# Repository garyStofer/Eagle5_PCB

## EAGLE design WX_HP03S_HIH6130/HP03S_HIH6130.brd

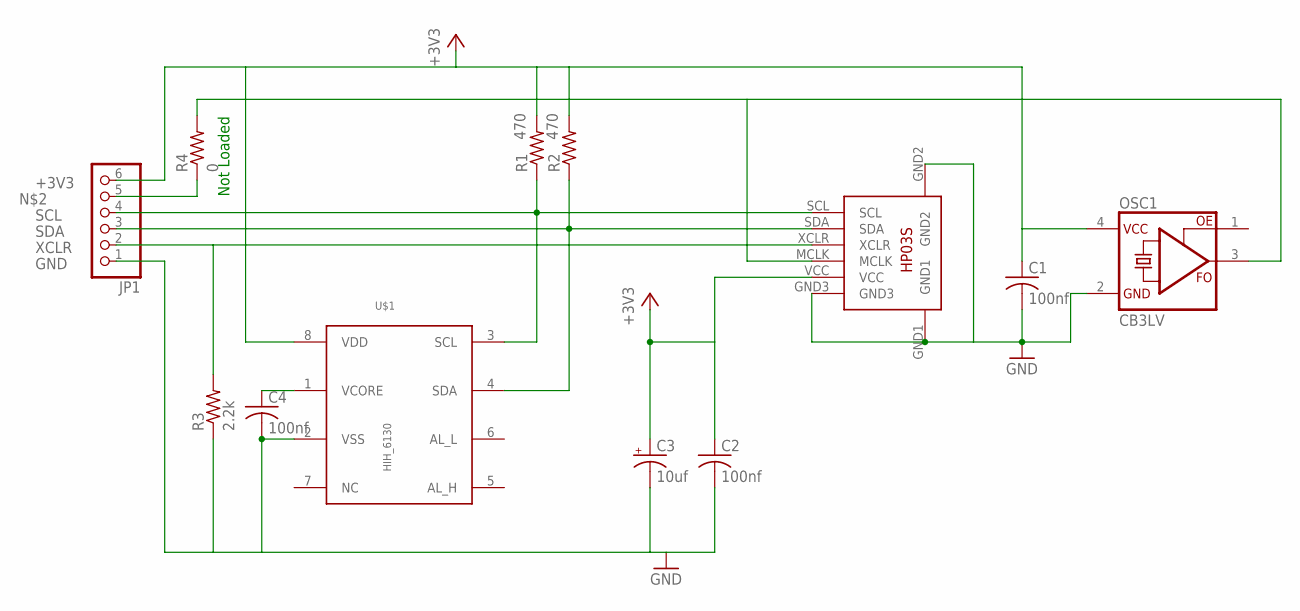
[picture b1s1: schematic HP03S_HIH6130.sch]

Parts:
C1: 100nf; C0805
C2, C4: 100nf; C0805K
C3: 10uf; SMC_P
JP1: PINHD-1X6; 1X06
OSC1: CB3LV; SMD7.5X5MM
R1, R2: 470; R0603
R3: 2.2k; R0603
R4: 0; R0603
U$1: HIH_6130; SOIC8
U$2: HP03S

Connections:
+3V3: C1.1, C2.1, C3.+, JP1.6, OSC1.4 (VCC), R1.2, R2.2, U$1.8 (VDD), U$2.VCC
GND: C1.2, C2.2, C3.-, C4.2, JP1.1, OSC1.2 (GND), R3.1, U$1.2 (VSS), U$2.GND1, U$2.GND2, U$2.GND3
unnamed: C4.1, U$1.1 (VCORE)
unnamed: JP1.5, R4.1
RTCCLK: OSC1.3 (FO), R4.2, U$2.MCLK
SCL: JP1.4, R1.1, U$1.3 (SCL), U$2.SCL
SDA: JP1.3, R2.1, U$1.4 (SDA), U$2.SDA
XCLR: JP1.2, R3.2, U$2.XCLR

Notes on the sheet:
Not Loaded

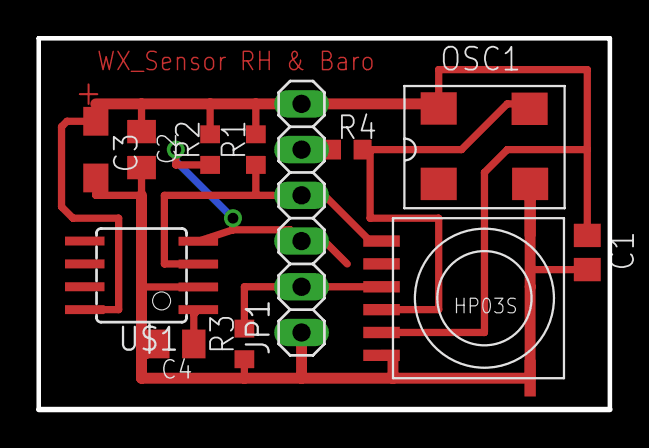
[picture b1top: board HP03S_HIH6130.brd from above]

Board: 2 copper layers, 31.7 x 20.6 mm, 12 parts (0 on the bottom side), 8 nets.

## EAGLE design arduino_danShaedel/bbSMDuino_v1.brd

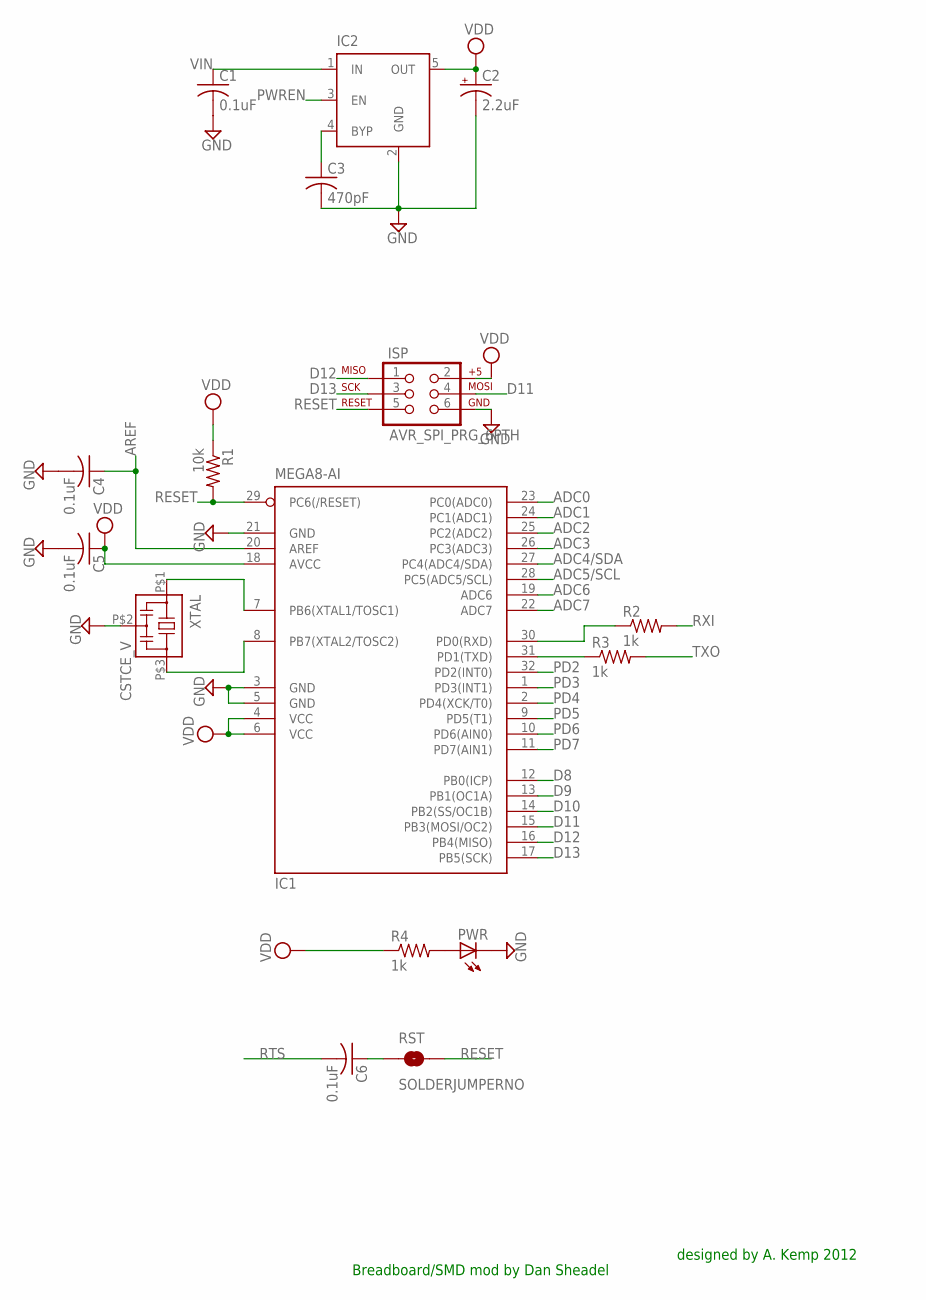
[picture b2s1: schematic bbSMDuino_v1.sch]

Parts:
C1, C4, C5, C6: 0.1uF; C0603
C2: 2.2uF; CT3216
C3: 470pF; C0603
IC1: MEGA8-AI; TQFP32-08
IC2: MIC5219XX; SOT23-5
ISP: AVR_SPI_PRG_6PTH; 2X3
PWR: LEDCHIP-LED0603; CHIP-LED0603
R1: 10k; R0603
R2, R3, R4: 1k; R0603
RST: SOLDERJUMPERNO; SJ_2S-NO
XTAL: CSTCE_V

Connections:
ADC0: IC1.23 (PC0(ADC0))
ADC1: IC1.24 (PC1(ADC1))
ADC2: IC1.25 (PC2(ADC2))
ADC3: IC1.26 (PC3(ADC3))
ADC4/SDA: IC1.27 (PC4(ADC4/SDA))
ADC5/SCL: IC1.28 (PC5(ADC5/SCL))
ADC6: IC1.19 (ADC6)
ADC7: IC1.22 (ADC7)
AREF: C4.1, IC1.20 (AREF)
D8: IC1.12 (PB0(ICP))
D9: IC1.13 (PB1(OC1A))
D10: IC1.14 (PB2(SS/OC1B))
D11: IC1.15 (PB3(MOSI/OC2)), ISP.4
D12: IC1.16 (PB4(MISO)), ISP.1
D13: IC1.17 (PB5(SCK)), ISP.3
GND: C1.2, C2.-, C3.2, C4.2, C5.2, IC1.3 (GND), IC1.5 (GND), IC1.21 (GND), IC2.2 (GND), ISP.6, PWR.C, XTAL.P$2 (2)
unnamed: C6.1, RST.1
unnamed: PWR.A, R4.2
unnamed: C3.1, IC2.4 (BYP)
unnamed: IC1.30 (PD0(RXD)), R2.1
unnamed: IC1.31 (PD1(TXD)), R3.1
PD2: IC1.32 (PD2(INT0))
PD3: IC1.1 (PD3(INT1))
PD4: IC1.2 (PD4(XCK/T0))
PD5: IC1.9 (PD5(T1))
PD6: IC1.10 (PD6(AIN0))
PD7: IC1.11 (PD7(AIN1))
PWREN: IC2.3 (EN)
RESET: IC1.29 (PC6(/RESET)), ISP.5, R1.2, RST.2
RTS: C6.2
RXI: R2.2
TXO: R3.2
VDD: C2.+, C5.1, IC1.4 (VCC), IC1.6 (VCC), IC1.18 (AVCC), IC2.5 (OUT), ISP.2, R1.1, R4.1
VIN: C1.1, IC2.1 (IN)
XTAL$1: IC1.7 (PB6(XTAL1/TOSC1)), XTAL.P$1 (1)
XTAL$2: IC1.8 (PB7(XTAL2/TOSC2)), XTAL.P$3 (3)

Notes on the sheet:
designed by A. Kemp 2012
Breadboard/SMD mod by Dan Sheadel

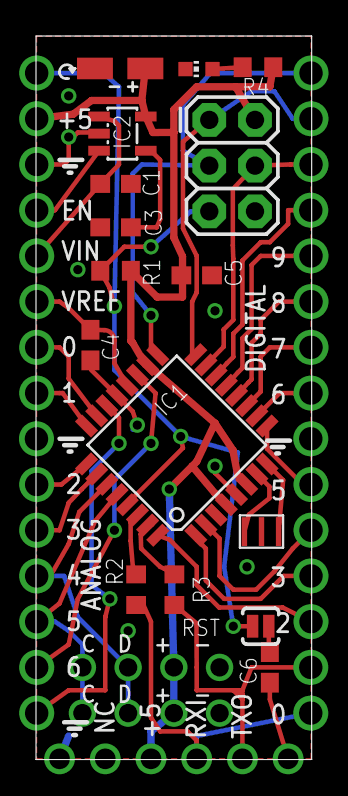
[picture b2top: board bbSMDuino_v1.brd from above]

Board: 2 copper layers, 15.3 x 40.2 mm, 16 parts (0 on the bottom side), 15 nets.

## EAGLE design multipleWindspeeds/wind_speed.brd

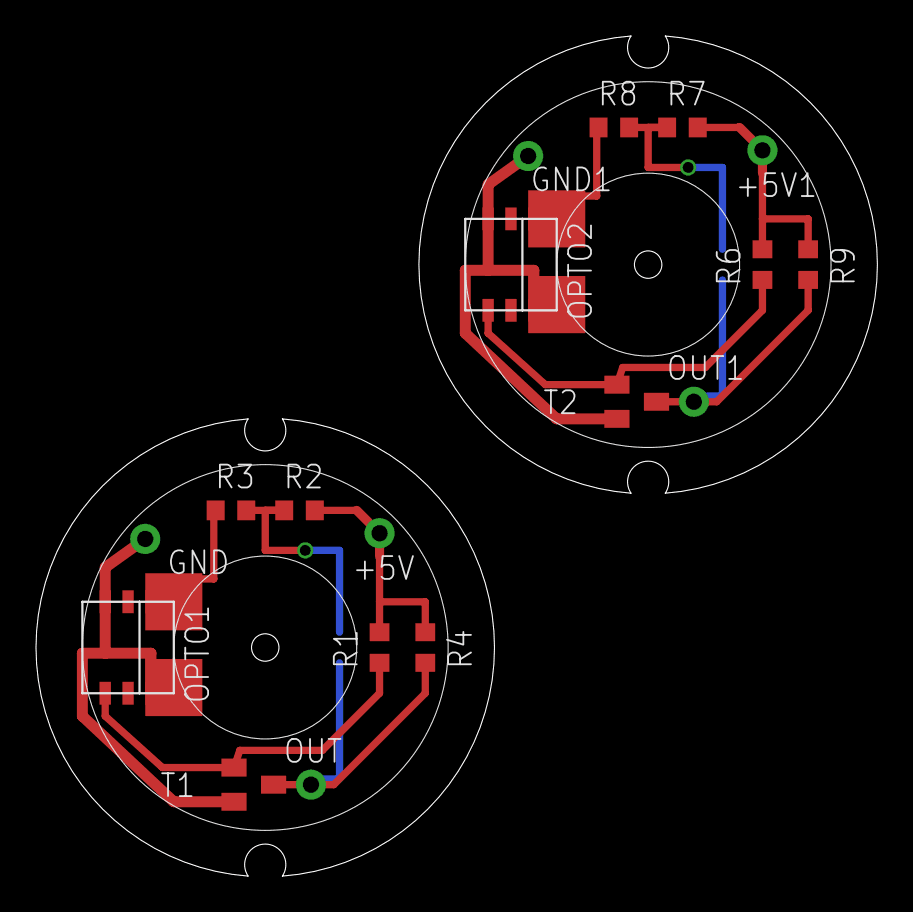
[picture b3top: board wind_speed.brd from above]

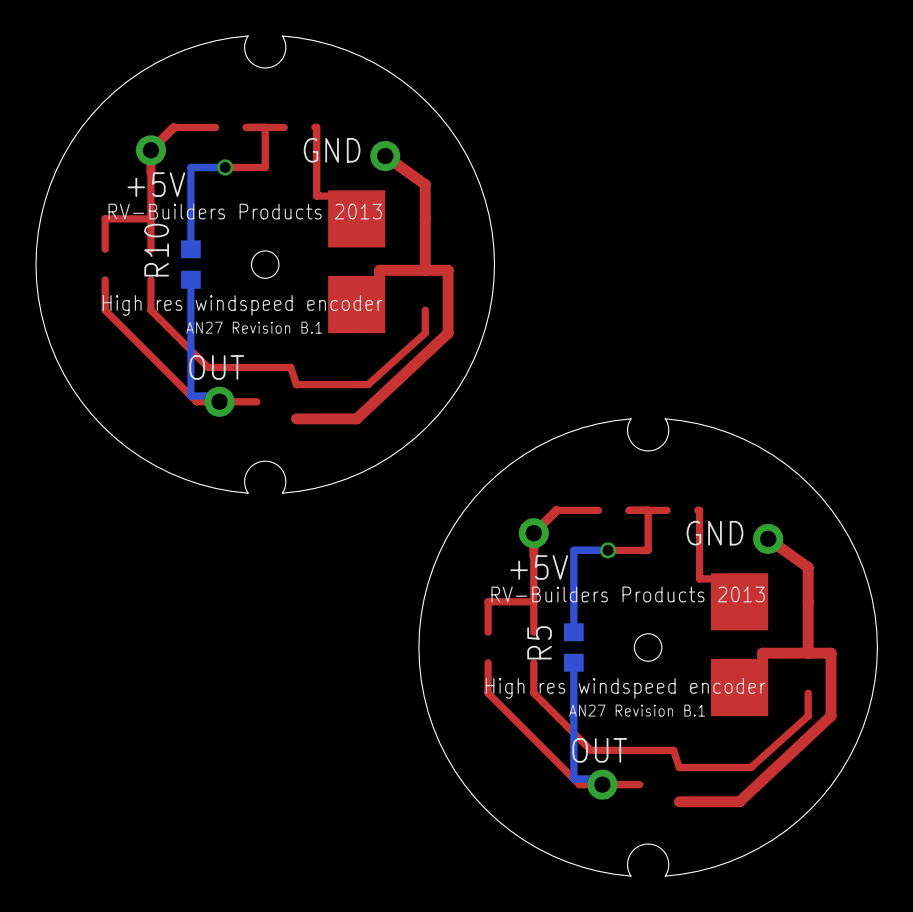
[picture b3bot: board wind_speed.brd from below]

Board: 2 copper layers, 46.7 x 46.7 mm, 20 parts (2 on the bottom side), 12 nets.

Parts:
+5V, +5V1: TPSOL; TP_SOL
GND, GND1: TPSOL; TP_SOL
OPTO1, OPTO2: OSRAM_SHF9201; OSRAM-6
OUT, OUT1: TPSOL; TP_SOL
R1, R6: 10K; R0603
R2, R3, R7, R8: 120o; R0603
R4, R9: 1K; R0603
R5, R10: 330; R0603
T1, T2: MMBT3904; SOT23

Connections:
unnamed: OPTO1.P$4, R1.1, T1.1
unnamed: GND.P$1, OPTO1.P$3, OPTO1.P$6, T1.2
unnamed: +5V.P$1, R1.2, R2.2, R4.2
unnamed: OUT.P$1, R4.1, R5.1, T1.3
unnamed: OPTO1.P$1, R3.1
unnamed: R2.1, R3.2, R5.2
unnamed: OPTO2.P$4, R6.1, T2.1
unnamed: GND1.P$1, OPTO2.P$3, OPTO2.P$6, T2.2
unnamed: +5V1.P$1, R6.2, R7.2, R9.2
unnamed: OUT1.P$1, R9.1, R10.1, T2.3
unnamed: OPTO2.P$1, R8.1
unnamed: R7.1, R8.2, R10.2

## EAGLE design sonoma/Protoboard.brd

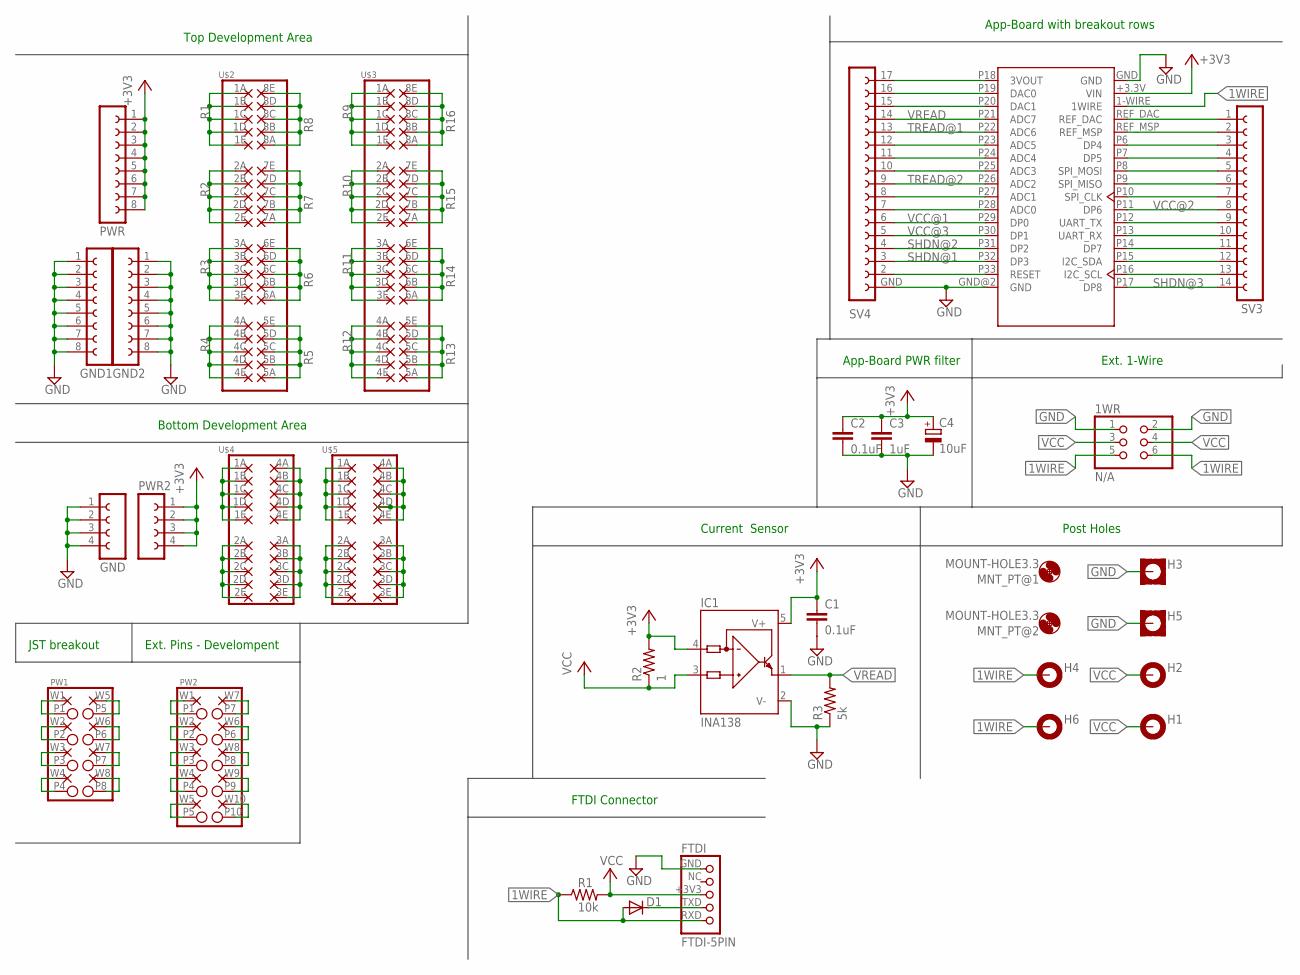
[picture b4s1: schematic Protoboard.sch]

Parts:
1WR: N/A; 2X03
C1, C2: 0.1uF; C0603
C3: 1uF; C0603
C4: 10uF; SMC_B
D1: 1N4148DO35-7; DO35-7
FTDI: FTDI-5PIN; 1X05
GND: FE04-GND
GND1, GND2: FE08-GND
H1, H2, H4, H6: MOUNT-PAD-ROUND3.3; 3,3-PAD
H3, H5: MOUNT-PAD-SQUARE3.3; 3,3-PAD-SQUARE
IC1: INA138; SOT23-5
MNT_PT@1, MNT_PT@2: MOUNT-HOLE3.3; 3,3
PW1: PIN-WIRE-2X8; 2X8
PW2: PIN-WIRE-2X10; 2X10
PWR: FE08
PWR2: FE04-1
R1: 10k; 0204/5
R2: 1; R0603
R3: 5k; R0805
SV3: FE14-1_ABBO
SV4: FE17-1_ABBO
U$1: App-Board 1.2/1.3; APPCORE_RECEIVER
U$2, U$3: PROTO-5X8; PROTO-5X08
U$4, U$5: PROTO-4X5; PROTO-4X05

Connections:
1WIRE: 1WR.5, 1WR.6, D1.A, FTDI.RXD, H4.B3,3, H6.B3,3, R1.1, U$1.1-WIRE (1WIRE)
+3V3: C1.1, C2.1, C3.1, C4.+, IC1.4 (IN-), IC1.5 (V+), PWR.1, PWR.2, PWR.3, PWR.4, PWR.5, PWR.6, PWR.7, PWR.8, PWR2.1, PWR2.2, PWR2.3, PWR2.4, R2.2, U$1.+3.3V (VIN)
GND: 1WR.1, 1WR.2, C1.2, C2.2, C3.2, C4.-, FTDI.GND, GND.1, GND.2, GND.3, GND.4, GND1.1, GND1.2, GND1.3, GND1.4, GND1.5, GND1.6, GND1.7, GND1.8, GND2.1, GND2.2, GND2.3, GND2.4, GND2.5, GND2.6, GND2.7, GND2.8, H3.B3,3, H5.B3,3, IC1.2 (V-), R3.1, SV4.GND, U$1.GND, U$1.GND@2 (GND)
unnamed: U$4.1A, U$4.1B, U$4.1C, U$4.1D, U$4.1E
unnamed: PW1.P1, PW1.W1
unnamed: D1.C, FTDI.TXD
unnamed: PW1.P2, PW1.W2
unnamed: U$4.4A, U$4.4B, U$4.4C, U$4.4D, U$4.4E
unnamed: U$4.2A, U$4.2B, U$4.2C, U$4.2D, U$4.2E
unnamed: U$4.3A, U$4.3B, U$4.3C, U$4.3D, U$4.3E
unnamed: U$5.1A, U$5.1B, U$5.1C, U$5.1D, U$5.1E
unnamed: U$5.4A, U$5.4B, U$5.4C, U$5.4D, U$5.4E
unnamed: U$5.2A, U$5.2B, U$5.2C, U$5.2D, U$5.2E
unnamed: U$5.3A, U$5.3B, U$5.3C, U$5.3D, U$5.3E
unnamed: PW2.P1, PW2.W1
unnamed: PW2.P2, PW2.W2
unnamed: PW2.P3, PW2.W3
unnamed: PW2.P4, PW2.W4
unnamed: PW2.P5, PW2.W5
unnamed: PW2.P7, PW2.W7
unnamed: PW2.P6, PW2.W6
unnamed: PW2.P8, PW2.W8
unnamed: PW2.P9, PW2.W9
unnamed: PW2.P10, PW2.W10
unnamed: SV3.1, U$1.REF_DAC
unnamed: SV3.2, U$1.REF_MSP
unnamed: SV3.3, U$1.P6 (DP4)
unnamed: SV3.4, U$1.P7 (DP5)
unnamed: SV3.5, U$1.P8 (SPI_MOSI)
unnamed: SV3.6, U$1.P9 (SPI_MISO)
unnamed: SV3.7, U$1.P10 (SPI_CLK)
unnamed: SV3.9, U$1.P12 (UART_TX)
unnamed: SV3.10, U$1.P13 (UART_RX)
unnamed: SV3.11, U$1.P14 (DP7)
unnamed: SV3.12, U$1.P15 (I2C_SDA)
unnamed: SV3.13, U$1.P16 (I2C_SCL)
unnamed: SV4.17, U$1.P18 (3VOUT)
unnamed: SV4.16, U$1.P19 (DAC0)
unnamed: SV4.15, U$1.P20 (DAC1)
unnamed: SV4.12, U$1.P23 (ADC5)
unnamed: SV4.11, U$1.P24 (ADC4)
unnamed: SV4.10, U$1.P25 (ADC3)
unnamed: SV4.8, U$1.P27 (ADC1)
unnamed: SV4.7, U$1.P28 (ADC0)
unnamed: PW1.P3, PW1.W3
unnamed: PW1.P4, PW1.W4
unnamed: PW1.P5, PW1.W5
unnamed: PW1.P6, PW1.W6
unnamed: PW1.P7, PW1.W7
unnamed: PW1.P8, PW1.W8
R1: U$2.1A, U$2.1B, U$2.1C, U$2.1D, U$2.1E
R2: U$2.2A, U$2.2B, U$2.2C, U$2.2D, U$2.2E
R3: U$2.3A, U$2.3B, U$2.3C, U$2.3D, U$2.3E
R4: U$2.4A, U$2.4B, U$2.4C, U$2.4D, U$2.4E
R5: U$2.5A, U$2.5B, U$2.5C, U$2.5D, U$2.5E
R6: U$2.6A, U$2.6B, U$2.6C, U$2.6D, U$2.6E
R7: U$2.7A, U$2.7B, U$2.7C, U$2.7D, U$2.7E
R8: U$2.8A, U$2.8B, U$2.8C, U$2.8D, U$2.8E
R9: U$3.1A, U$3.1B, U$3.1C, U$3.1D, U$3.1E
R10: U$3.2A, U$3.2B, U$3.2C, U$3.2D, U$3.2E
R11: U$3.3A, U$3.3B, U$3.3C, U$3.3D, U$3.3E
R12: U$3.4A, U$3.4B, U$3.4C, U$3.4D, U$3.4E
R13: U$3.5A, U$3.5B, U$3.5C, U$3.5D, U$3.5E
R14: U$3.6A, U$3.6B, U$3.6C, U$3.6D, U$3.6E
R15: U$3.7A, U$3.7B, U$3.7C, U$3.7D, U$3.7E
R16: U$3.8A, U$3.8B, U$3.8C, U$3.8D, U$3.8E
RESET: SV4.2, U$1.P33 (RESET)
SHDN@1: SV4.3, U$1.P32 (DP3)
SHDN@2: SV4.4, U$1.P31 (DP2)
SHDN@3: SV3.14, U$1.P17 (DP8)
TREAD@1: SV4.13, U$1.P22 (ADC6)
TREAD@2: SV4.9, U$1.P26 (ADC2)
VCC: 1WR.3, 1WR.4, FTDI.+3V3, H1.B3,3, H2.B3,3, IC1.3 (IN+), R1.2, R2.1
VCC@1: SV4.6, U$1.P29 (DP0)
VCC@2: SV3.8, U$1.P11 (DP6)
VCC@3: SV4.5, U$1.P30 (DP1)
VREAD: IC1.1 (OUT), R3.2, SV4.14, U$1.P21 (ADC7)

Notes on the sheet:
Post Holes
Ext. 1-Wire
App-Board with breakout rows
App-Board PWR filter
Current Sensor
FTDI Connector
JST breakout
Ext. Pins - Develompent
Bottom Development Area
Top Development Area

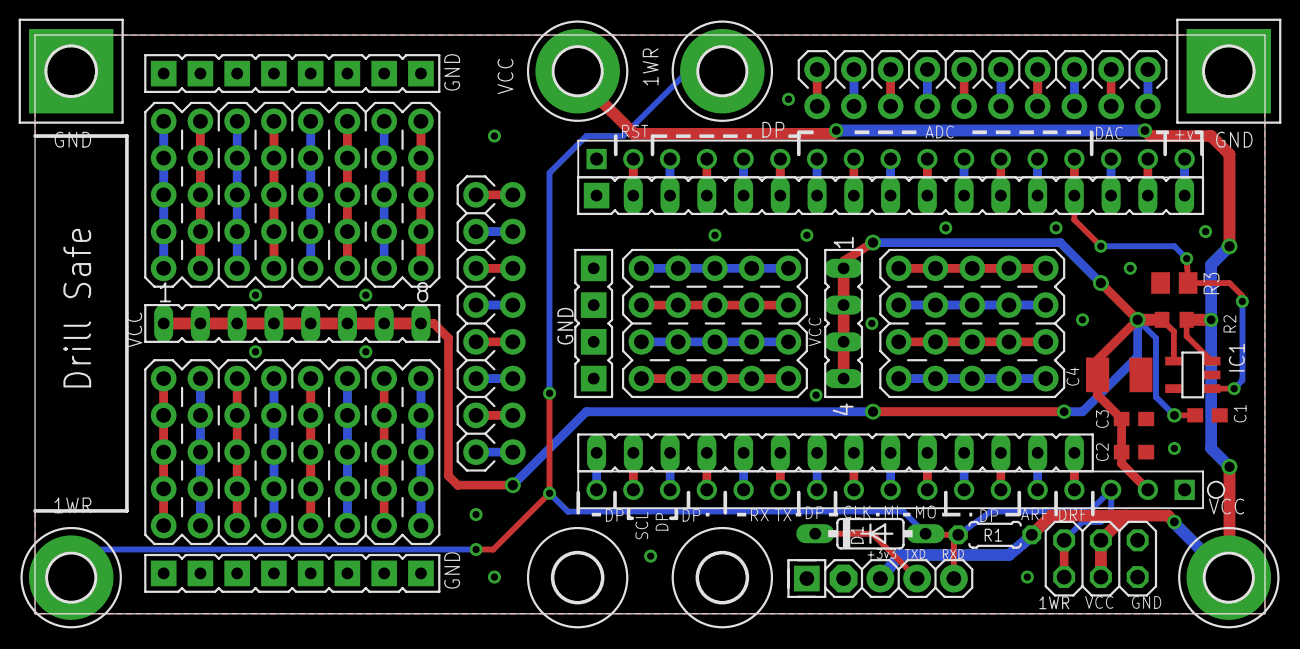
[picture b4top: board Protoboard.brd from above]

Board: 2 copper layers, 85.0 x 40.0 mm, 33 parts (0 on the bottom side), 77 nets.

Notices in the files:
WX_HP03S_HIH6130/HP03S_HIH6130.brd:
RV Builders ©2012
parts and their libraries:
SparkFun-Connectors: Licensing: CC v3.0 Share-Alike You are welcome to use this library for commercial purposes.
